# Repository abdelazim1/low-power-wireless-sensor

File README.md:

## low-power-wireless-sensor
low_power wireless sensor (gas detection) S/W_H/W based on stm32f103 MCU
#I am going to slove bugs and complete the project

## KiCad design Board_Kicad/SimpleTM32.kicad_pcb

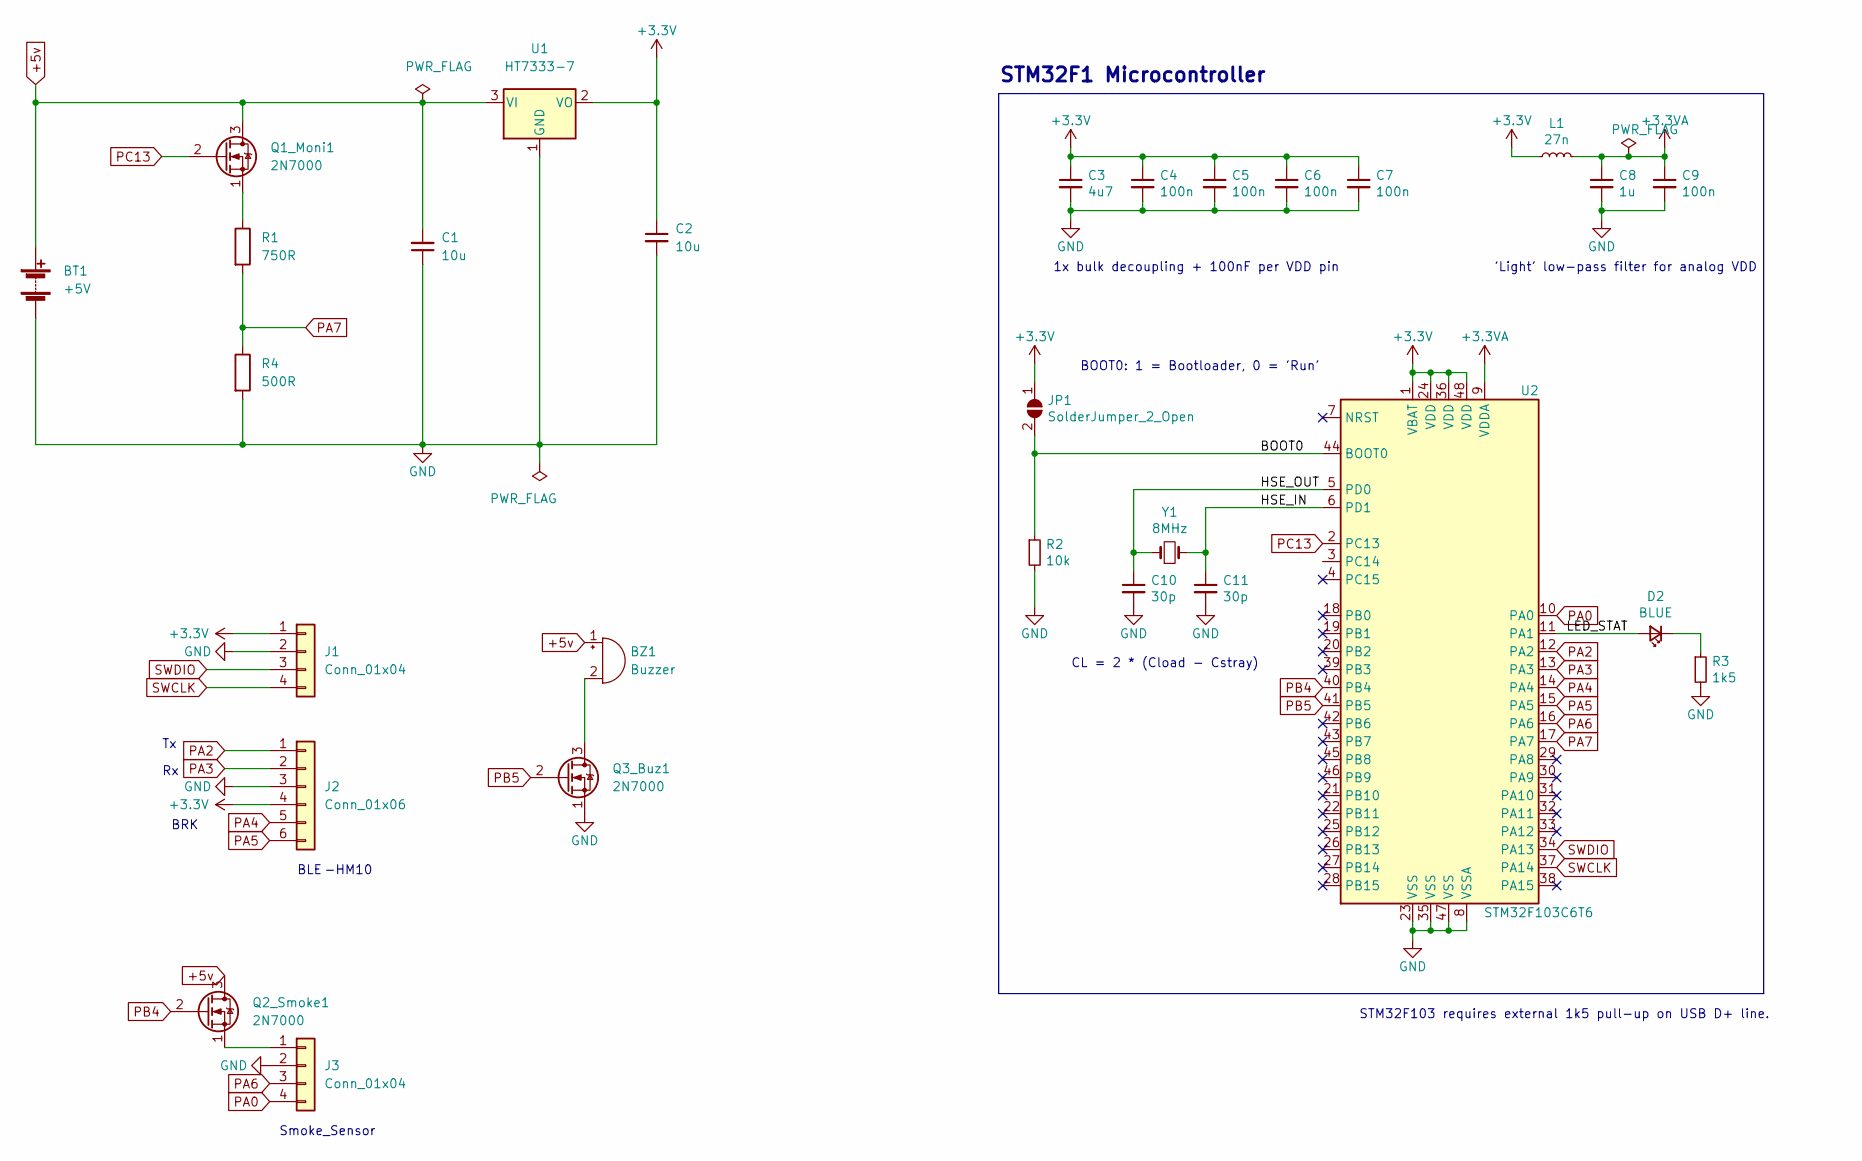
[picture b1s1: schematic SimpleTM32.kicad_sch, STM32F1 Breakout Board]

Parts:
BT1: +5V; BatteryHolder_ComfortableElectronic_CH273-2450_1x2450
BZ1: Buzzer; Buzzer_12x9.5RM7.6
C1, C2: 10u; C_Radial_D5.0mm_H5.0mm_P2.00mm
C3: 4u7; C_0603_1608Metric; LCSC Part # C19666
C4, C5, C6, C7, C9: 100n; C_0402_1005Metric; LCSC Part # C1525
C8: 1u; C_0402_1005Metric; LCSC Part # C52923
C10, C11: 30p; C_0402_1005Metric; LCSC Part # C1570
D2: BLUE; LED_0603_1608Metric; LCSC Part # C72041
J1: Conn_01x04; PinHeader_1x04_P1.27mm_Vertical
J2: Conn_01x06; PinSocket_1x06_P1.27mm_Vertical
J3: Conn_01x04; PinSocket_1x04_P1.27mm_Vertical
JP1: SolderJumper_2_Open; SolderJumper-2_P1.3mm_Open_Pad1.0x1.5mm
L1: 27n; L_0402_1005Metric; LCSC Part # C18830
Q1_Moni1, Q2_Smoke1, Q3_Buz1: 2N7000; TO-92_Inline
R1: 750R; R_Axial_DIN0204_L3.6mm_D1.6mm_P5.08mm_Vertical
R2: 10k; R_0402_1005Metric; LCSC Part # C25744
R3: 1k5; R_0603_1608Metric; LCSC Part # C22843
R4: 500R; R_Axial_DIN0204_L3.6mm_D1.6mm_P5.08mm_Vertical
U1: HT7333-7; SOT-223-3_TabPin2
U2: STM32F103C6T6; LQFP-48_7x7mm_P0.5mm; LCSC Part # C8734
Y1: 8MHz; Crystal_SMD_5032-2Pin_5.0x3.2mm; LCSC Part # C115962

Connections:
+3.3V: C2.1, C3.1, C4.1, C5.1, C6.1, C7.1, J1.1, J2.4, JP1.1 (A), L1.1, U1.2 (VO), U2.1 (VBAT), U2.24 (VDD), U2.36 (VDD), U2.48 (VDD)
+3.3VA: C8.1, C9.1, L1.2, U2.9 (VDDA)
+5v: BT1.1 (+), BZ1.1 (-), C1.2, Q1_Moni1.3 (D), Q2_Smoke1.3 (D), U1.3 (VI)
/BOOT0: JP1.2 (B), R2.1, U2.44 (BOOT0)
/HSE_IN: C11.1, U2.6 (PD1), Y1.2
/HSE_OUT: C10.1, U2.5 (PD0), Y1.1
/LED_STAT: D2.2 (A), U2.11 (PA1)
GND: BT1.2 (-), C1.1, C2.2, C3.2, C4.2, C5.2, C6.2, C7.2, C8.2, C9.2, C10.2, C11.2, J1.2, J2.3, J3.2, Q3_Buz1.1 (S), R2.2, R3.2, R4.2, U1.1 (GND), U2.8 (VSSA), U2.23 (VSS), U2.35 (VSS), U2.47 (VSS)
unnamed: BZ1.2 (+), Q3_Buz1.3 (D)
unnamed: D2.1 (K), R3.1
unnamed: J3.1, Q2_Smoke1.1 (S)
unnamed: Q1_Moni1.1 (S), R1.1
PA0: J3.4, U2.10 (PA0)
PA2: J2.1, U2.12 (PA2)
PA3: J2.2, U2.13 (PA3)
PA4: J2.5, U2.14 (PA4)
PA5: J2.6, U2.15 (PA5)
PA6: J3.3, U2.16 (PA6)
PB4: Q2_Smoke1.2 (G), U2.40 (PB4)
PB5: Q3_Buz1.2 (G), U2.41 (PB5)
PC13: Q1_Moni1.2 (G), U2.2 (PC13)
PC14: R1.2, R4.1, U2.3 (PC14), U2.17 (PA7)
SWCLK: J1.4, U2.37 (PA14)
SWDIO: J1.3, U2.34 (PA13)

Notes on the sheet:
BOOT0: 1 = Bootloader, 0 = 'Run'
BRK
CL = 2 * (Cload - Cstray)
-HM10
Smoke_Sensor
STM32F103 requires external 1k5 pull-up on USB D+ line.
BLE
STM32F1 Microcontroller
1x bulk decoupling + 100nF per VDD pin
'Light' low-pass filter for analog VDD

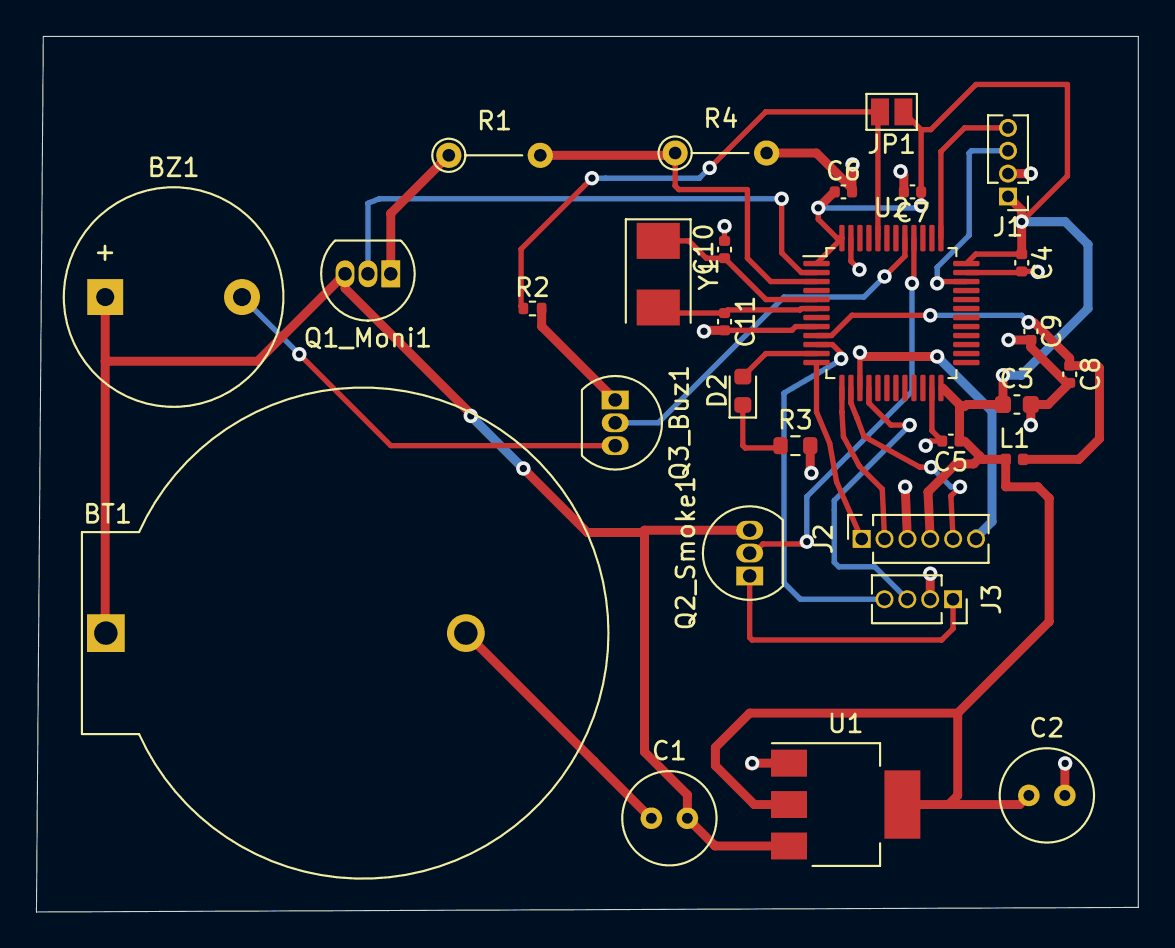
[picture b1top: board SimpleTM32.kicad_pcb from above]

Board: 2 copper layers, 61.2 x 48.6 mm, 29 parts (0 on the bottom side), 24 nets.

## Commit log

2022-12-24 V1.0
2022-12-24 ReadmeV1.
